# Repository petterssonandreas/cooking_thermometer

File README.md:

# cooking_thermometer

Simple electronics and SW project for creating a digital cooking/meat thermometer.

A probe from an old broken thermometer is used. The probe appears to be an NTC with around 200k resistance at 25C. Tests done at different temps to get a curve for the probe, curve can be found in `adc.c`.

The probe is connected to the HW via a 2.5mm "mono" jack with tip detection.

The processor used is an STM32G0B0KE with 512 kB flash and 144 kB SRAM. It comes in a LQFP32 package.

The product is powered via USB or via a 3.6V Li-ion battery, which is also charged when USB is connected. The battery is recycled from another old product. A small MCP73831 is used for the battery charging.

A small OLED display is used to display temperature and other info.

An active buzzer is used for the alarm functionality.

The system runs on 3.3 V.

# Zephyr installation

### Clone this repo
```
git clone git@github.com:petterssonandreas/cooking_thermometer.git
```

### Create a virtualenv, source it
```
python3 -m venv .venv
source .venv/Scripts/activate
```

### Install west
```
pip3 install west
```

### Init west with local repo, update
```
west init -l cooking_thermometer/
west update
```

### Export CMake
```
west zephyr-export
```

### Install packages
```
west packages pip --install
```

### Install Zephyr SDK
```
west sdk install
```

# Project build and flash
```
west build -p always -b ct_g0b0ke cooking_thermometer/apps/ct/
west flash
```

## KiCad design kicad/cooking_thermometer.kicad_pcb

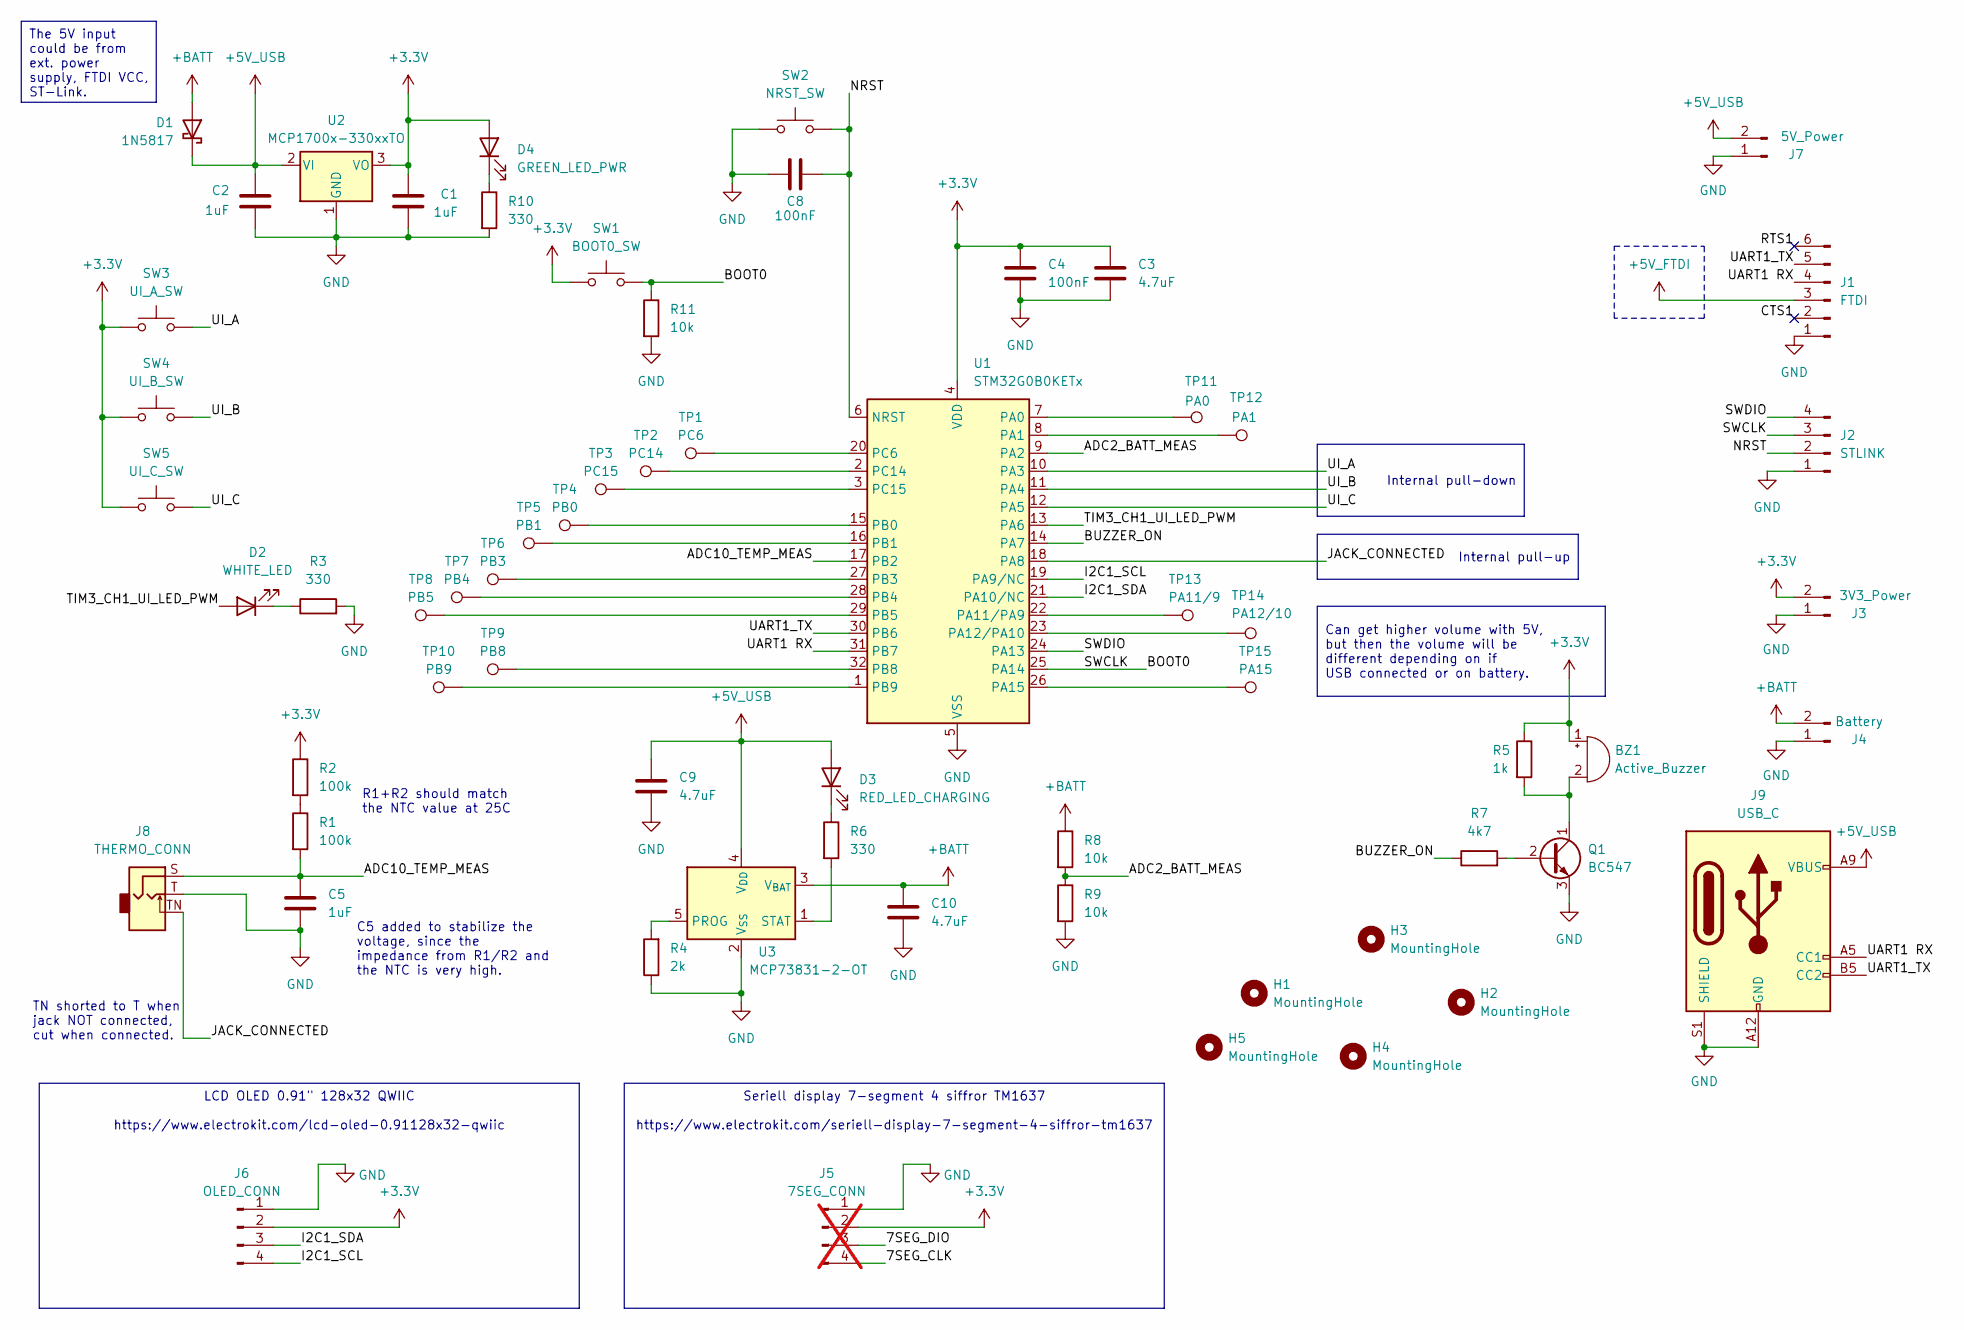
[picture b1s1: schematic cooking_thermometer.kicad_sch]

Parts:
BZ1: Active_Buzzer; Buzzer_12x9.5RM7.6
C1, C2, C5: 1uF; C_1206_3216Metric_Pad1.33x1.80mm_HandSolder
C3, C9, C10: 4.7uF; C_1206_3216Metric_Pad1.33x1.80mm_HandSolder
C4, C8: 100nF; C_1206_3216Metric_Pad1.33x1.80mm_HandSolder
D1: 1N5817; D_DO-41_SOD81_P10.16mm_Horizontal
D2: WHITE_LED; LED_D4.0mm
D3: RED_LED_CHARGING; LED_Rectangular_W5.0mm_H2.0mm
D4: GREEN_LED_PWR; LED_Rectangular_W5.0mm_H2.0mm
H1, H2, H3, H4, H5: MountingHole; MountingHole_3.2mm_M3
J1: FTDI; PinHeader_1x06_P2.54mm_Vertical
J2: STLINK; PinHeader_1x04_P2.54mm_Vertical
J3: 3V3_Power; PinHeader_1x02_P2.54mm_Vertical
J4: Battery; PinHeader_1x02_P2.54mm_Vertical
J5: 7SEG_CONN; PinSocket_1x04_P2.54mm_Vertical; not fitted
J6: OLED_CONN; PinHeader_1x04_P2.54mm_Vertical
J7: 5V_Power; PinHeader_1x02_P2.54mm_Vertical
J8: THERMO_CONN; Jack_Mono_2.5mm_with_Tip-Detect_Electrokit_41010270
J9: USB_C; USB_C_Receptacle_6P_TopMnt_Horizontal_Long_Pads_Electrokit_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
Q1: BC547; TO-92L_Inline_Wide
R1, R2: 100k; R_1206_3216Metric_Pad1.30x1.75mm_HandSolder
R3, R6, R10: 330; R_1206_3216Metric_Pad1.30x1.75mm_HandSolder
R4: 2k; R_1206_3216Metric_Pad1.30x1.75mm_HandSolder
R5: 1k; R_1206_3216Metric_Pad1.30x1.75mm_HandSolder
R7: 4k7; R_1206_3216Metric_Pad1.30x1.75mm_HandSolder
R8, R9, R11: 10k; R_1206_3216Metric_Pad1.30x1.75mm_HandSolder
SW1: BOOT0_SW; SW_PUSH_6mm
SW2: NRST_SW; SW_PUSH_6mm
SW3: UI_A_SW; SW_PUSH_6mm
SW4: UI_B_SW; SW_PUSH_6mm
SW5: UI_C_SW; SW_PUSH_6mm
TP1: PC6; TestPoint_Pad_D2.0mm
TP2: PC14; TestPoint_Pad_D2.0mm
TP3: PC15; TestPoint_Pad_D2.0mm
TP4: PB0; TestPoint_Pad_D2.0mm
TP5: PB1; TestPoint_Pad_D2.0mm
TP6: PB3; TestPoint_Pad_D2.0mm
TP7: PB4; TestPoint_Pad_D2.0mm
TP8: PB5; TestPoint_Pad_D2.0mm
TP9: PB8; TestPoint_Pad_D2.0mm
TP10: PB9; TestPoint_Pad_D2.0mm
TP11: PA0; TestPoint_Pad_D2.0mm
TP12: PA1; TestPoint_Pad_D2.0mm
TP13: PA11/9; TestPoint_Pad_D2.0mm
TP14: PA12/10; TestPoint_Pad_D2.0mm
TP15: PA15; TestPoint_Pad_D2.0mm
U1: STM32G0B0KETx; LQFP-32_7x7mm_P0.8mm_Long_pads
U2: MCP1700x-330xxTO; TO-92_Inline
U3: MCP73831-2-OT; SOT-23-5_HandSoldering

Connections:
+3.3V: BZ1.1 (+), C1.1, C3.1, C4.1, D4.2 (A), J3.2, J5.2, J6.2, R2.1, R5.1, SW1.1, SW3.1, SW4.1, SW5.1, U1.4 (VDD), U2.3 (VO)
+5V_FTDI: J1.3
+5V_USB: C2.1, C9.1, D1.1 (K), D3.2 (A), J7.2, J9.A9 (VBUS), J9.B9 (VBUS), U2.2 (VI), U3.4 (V_{DD})
+BATT: C10.1, D1.2 (A), J4.2, R8.1, U3.3 (V_{BAT})
/ADC2_BATT_MEAS: R8.2, R9.1, U1.9 (PA2)
/ADC10_TEMP_MEAS: C5.1, J8.S, R1.2, U1.17 (PB2)
/BOOT0: J2.3, R11.1, SW1.2, U1.25 (PA14)
/BUZZER_ON: R7.1, U1.14 (PA7)
/CTS1: J1.2
/I2C1_SCL: J6.4, U1.19 (PA9/NC)
/I2C1_SDA: J6.3, U1.21 (PA10/NC)
/JACK_CONNECTED: J8.TN, U1.18 (PA8)
/NRST: C8.2, J2.2, SW2.2, U1.6 (NRST)
/RTS1: J1.6
/SWDIO: J2.4, U1.24 (PA13)
/TIM3_CH1_UI_LED_PWM: D2.2 (A), U1.13 (PA6)
/UART1 RX: J1.4, J9.A5 (CC1), U1.31 (PB7)
/UART1_TX: J1.5, J9.B5 (CC2), U1.30 (PB6)
/UI_A: SW3.2, U1.10 (PA3)
/UI_B: SW4.2, U1.11 (PA4)
/UI_C: SW5.2, U1.12 (PA5)
GND: C1.2, C2.2, C3.2, C4.2, C5.2, C8.1, C9.2, C10.2, J1.1, J2.1, J3.1, J4.1, J5.1, J6.1, J7.1, J8.T, J9.A12 (GND), J9.B12 (GND), J9.S1 (SHIELD), Q1.3 (E), R3.2, R4.1, R9.2, R10.2, R11.2, SW2.1, U1.5 (VSS), U2.1 (GND), U3.2 (V_{SS})
unnamed: BZ1.2 (-), Q1.1 (C), R5.2
unnamed: D2.1 (K), R3.1
unnamed: D3.1 (K), R6.1
unnamed: D4.1 (K), R10.1
unnamed: Q1.2 (B), R7.2
unnamed: R1.1, R2.2
unnamed: TP11.1, U1.7 (PA0)
unnamed: TP12.1, U1.8 (PA1)
unnamed: TP13.1, U1.22 (PA11/PA9)
unnamed: TP14.1, U1.23 (PA12/PA10)
unnamed: TP15.1, U1.26 (PA15)
unnamed: TP4.1, U1.15 (PB0)
unnamed: TP5.1, U1.16 (PB1)
unnamed: TP6.1, U1.27 (PB3)
unnamed: TP7.1, U1.28 (PB4)
unnamed: TP8.1, U1.29 (PB5)
unnamed: TP9.1, U1.32 (PB8)
unnamed: TP10.1, U1.1 (PB9)
unnamed: TP1.1, U1.20 (PC6)
unnamed: TP2.1, U1.2 (PC14)
unnamed: TP3.1, U1.3 (PC15)
unnamed: R4.2, U3.5 (PROG)
unnamed: R6.2, U3.1 (STAT)

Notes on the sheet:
Can get higher volume with 5V, but then the volume will be different depending on if USB connected or on battery.
LCD OLED 0.91" 128x32 QWIIC https://www.electrokit.com/lcd-oled-0.91128x32-qwiic
Internal pull-down
Internal pull-up
The 5V input could be from ext. power supply, FTDI VCC, ST-Link.
Seriell display 7-segment 4 siffror TM1637 https://www.electrokit.com/seriell-display-7-segment-4-siffror-tm1637
TN shorted to T when jack NOT connected, cut when connected.
R1+R2 should match the NTC value at 25C
C5 added to stabilize the voltage, since the impedance from R1/R2 and the NTC is very high.

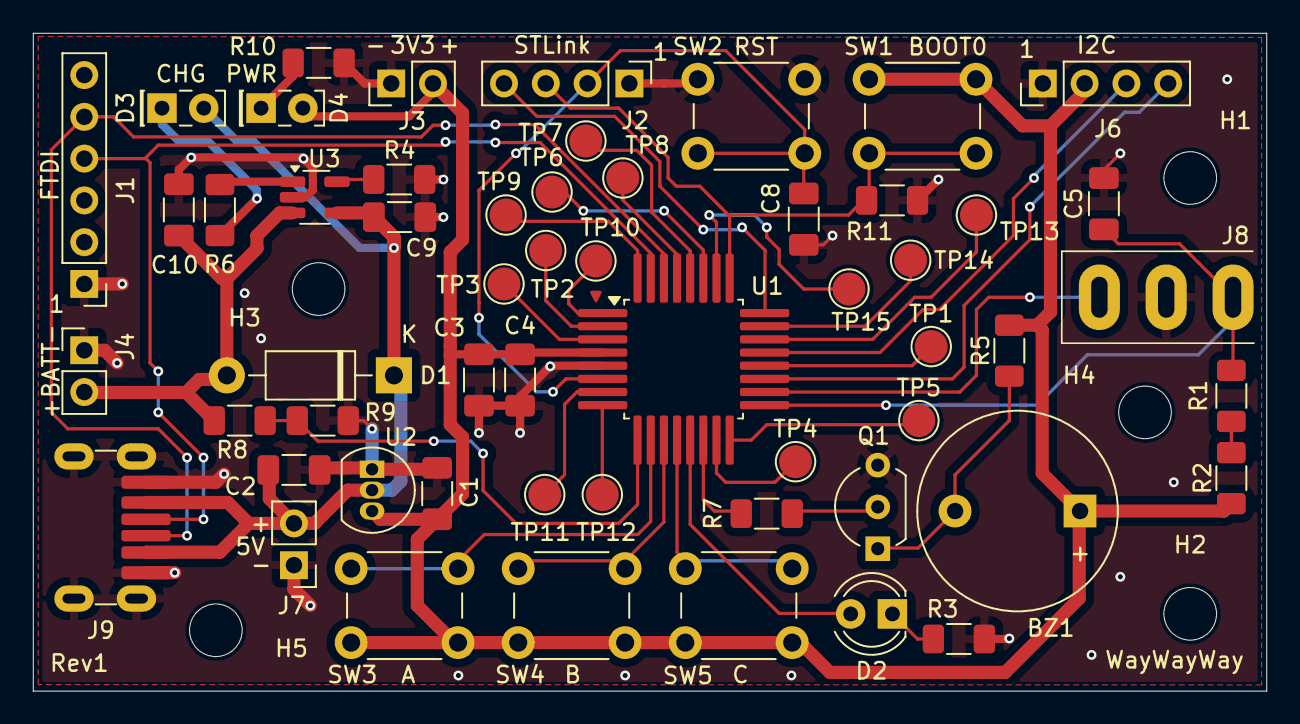
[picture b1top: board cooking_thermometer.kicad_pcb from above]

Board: 2 copper layers, 75.0 x 40.0 mm, 61 parts (0 on the bottom side), 42 nets.

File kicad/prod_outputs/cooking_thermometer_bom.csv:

"Id";"Designator";"Footprint";"Quantity";"Designation";"Supplier and ref";
1;"TP2";"TestPoint_Pad_D2.0mm";1;"PC14";;;
2;"R3,R6,R10";"R_1206_3216Metric_Pad1.30x1.75mm_HandSolder";3;"330";;;
3;"SW4";"SW_PUSH_6mm";1;"UI_B_SW";;;
4;"R8,R9,R1,R2";"R_1206_3216Metric_Pad1.30x1.75mm_HandSolder";4;"100k";;;
5;"SW5";"SW_PUSH_6mm";1;"UI_C_SW";;;
6;"U1";"LQFP-32_7x7mm_P0.8mm_Long_pads";1;"STM32G0B0KETx";;;
7;"C10,C3,C9";"C_1206_3216Metric_Pad1.33x1.80mm_HandSolder";3;"4.7uF";;;
8;"J3";"PinHeader_1x02_P2.54mm_Vertical";1;"3V3_Power";;;
9;"TP8";"TestPoint_Pad_D2.0mm";1;"PB5";;;
10;"R5";"R_1206_3216Metric_Pad1.30x1.75mm_HandSolder";1;"1k";;;
11;"J4";"PinHeader_1x02_P2.54mm_Vertical";1;"Battery";;;
12;"C8,C4";"C_1206_3216Metric_Pad1.33x1.80mm_HandSolder";2;"100nF";;;
13;"TP10";"TestPoint_Pad_D2.0mm";1;"PB9";;;
14;"D1";"D_DO-41_SOD81_P10.16mm_Horizontal";1;"1N5817";;;
15;"D4";"LED_Rectangular_W5.0mm_H2.0mm";1;"GREEN_LED_PWR";;;
16;"J8";"Jack_Mono_2.5mm_with_Tip-Detect_Electrokit_41010270";1;"THERMO_CONN";;;
17;"U3";"SOT-23-5_HandSoldering";1;"MCP73831-2-OT";;;
18;"U2";"TO-92_Inline";1;"MCP1700x-330xxTO";;;
19;"TP13";"TestPoint_Pad_D2.0mm";1;"PA11/9";;;
20;"J9";"USB_C_Receptacle_6P_TopMnt_Horizontal_Long_Pads_Electrokit_41021035";1;"USB_C";;;
21;"TP9";"TestPoint_Pad_D2.0mm";1;"PB8";;;
22;"D3";"LED_Rectangular_W5.0mm_H2.0mm";1;"RED_LED_CHARGING";;;
23;"TP6";"TestPoint_Pad_D2.0mm";1;"PB3";;;
24;"TP5";"TestPoint_Pad_D2.0mm";1;"PB1";;;
25;"J2";"PinHeader_1x04_P2.54mm_Vertical";1;"STLINK";;;
26;"J7";"PinHeader_1x02_P2.54mm_Vertical";1;"5V_Power";;;
27;"R7";"R_1206_3216Metric_Pad1.30x1.75mm_HandSolder";1;"4k7";;;
28;"TP14";"TestPoint_Pad_D2.0mm";1;"PA12/10";;;
29;"R11";"R_1206_3216Metric_Pad1.30x1.75mm_HandSolder";1;"10k";;;
30;"TP1";"TestPoint_Pad_D2.0mm";1;"PC6";;;
31;"BZ1";"Buzzer_12x9.5RM7.6";1;"Passive_Buzzer";;;
32;"C2,C1";"C_1206_3216Metric_Pad1.33x1.80mm_HandSolder";2;"1uF";;;
33;"Q1";"TO-92L_Inline_Wide";1;"BC547";;;
34;"TP4";"TestPoint_Pad_D2.0mm";1;"PB0";;;
35;"TP11";"TestPoint_Pad_D2.0mm";1;"PA0";;;
36;"SW1";"SW_PUSH_6mm";1;"BOOT0_SW";;;
37;"TP12";"TestPoint_Pad_D2.0mm";1;"PA1";;;
38;"TP15";"TestPoint_Pad_D2.0mm";1;"PA15";;;
39;"J1";"PinHeader_1x06_P2.54mm_Vertical";1;"FTDI";;;
40;"J6";"PinHeader_1x04_P2.54mm_Vertical";1;"OLED_CONN";;;
41;"R4";"R_1206_3216Metric_Pad1.30x1.75mm_HandSolder";1;"2k";;;
42;"SW2";"SW_PUSH_6mm";1;"NRST_SW";;;
43;"TP3";"TestPoint_Pad_D2.0mm";1;"PC15";;;
44;"SW3";"SW_PUSH_6mm";1;"UI_A_SW";;;
45;"TP7";"TestPoint_Pad_D2.0mm";1;"PB4";;;
46;"D2";"LED_D4.0mm";1;"WHITE_LED";;;

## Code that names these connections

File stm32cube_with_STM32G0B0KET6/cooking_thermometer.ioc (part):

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Mcu.Name=STM32G0B0KETx
Mcu.Package=LQFP32
Mcu.UserName=STM32G0B0KETx
PA10.Mode=I2C
PA10.Signal=I2C1_SDA
PA13.Mode=Serial_Wire
PA13.Signal=SYS_SWDIO
PA14-BOOT0.Mode=Serial_Wire
PA14-BOOT0.Signal=SYS_SWCLK
PA2.Mode=IN2
PA2.Signal=ADC1_IN2
PA3.GPIOParameters=GPIO_Label
PA3.GPIO_Label=UI_A
PA3.Signal=GPIO_Input
PA4.GPIOParameters=GPIO_Label
PA4.GPIO_Label=UI_B
PA4.Signal=GPIO_Input
PA5.GPIOParameters=GPIO_Label
PA5.GPIO_Label=UI_C
PA5.Signal=GPIO_Input
PA6.GPIOParameters=GPIO_Label
PA6.GPIO_Label=UI_LED
PA6.Signal=GPIO_Output
PA7.Signal=S_TIM3_CH2
PA8.GPIOParameters=GPIO_Label
PA8.GPIO_Label=nJACK_CONN
PA8.Signal=GPIO_Input
PA9.Mode=I2C
PA9.Signal=I2C1_SCL
PB2.Mode=IN10
PB2.Signal=ADC1_IN10
PB6.Mode=Asynchronous
PB6.Signal=USART1_TX
PB7.Mode=Asynchronous
PB7.Signal=USART1_RX
RCC.HSE_VALUE=8000000
RCC.SYSCLKFreq_VALUE=16000000
board=custom

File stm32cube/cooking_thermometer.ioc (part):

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Mcu.Name=STM32F070F6Px
Mcu.Package=TSSOP20
Mcu.UserName=STM32F070F6Px
PA0.GPIOParameters=GPIO_Label
PA0.GPIO_Label=UI_LED
PA0.Signal=GPIO_Output
PA1.GPIOParameters=GPIO_Label
PA1.GPIO_Label=ADC1_BATT_MEAS
PA1.Mode=IN1
PA1.Signal=ADC_IN1
PA10.Mode=Asynchronous
PA10.Signal=USART1_RX
PA13.Mode=Serial_Wire
PA13.Signal=SYS_SWDIO
PA14.Mode=Serial_Wire
PA14.Signal=SYS_SWCLK
PA2.GPIOParameters=GPIO_PuPd,GPIO_Label
PA2.GPIO_Label=UI_B
PA2.GPIO_PuPd=GPIO_PULLDOWN
PA2.Signal=GPIO_Input
PA3.GPIOParameters=GPIO_PuPd,GPIO_Label
PA3.GPIO_Label=UI_A
PA3.GPIO_PuPd=GPIO_PULLDOWN
PA3.Signal=GPIO_Input
PA4.GPIOParameters=GPIO_Label
PA4.GPIO_Label=TIM14_CH1_BUZZER_PWM
PA4.Signal=S_TIM14_CH1
PA5.GPIOParameters=GPIO_PuPd,GPIO_Label
PA5.GPIO_Label=UI_C
PA5.GPIO_PuPd=GPIO_PULLDOWN
PA5.Signal=GPIO_Input
PA7.GPIOParameters=GPIO_PuPd,GPIO_Label
PA7.GPIO_Label=nJACK_CONNECTED
PA7.GPIO_PuPd=GPIO_PULLUP
PA7.Signal=GPIO_Input
PA9.Mode=Asynchronous
PA9.Signal=USART1_TX
PB1.GPIOParameters=GPIO_Label
PB1.GPIO_Label=ADC9_TEMP_MEAS
PB1.Mode=IN9
PB1.Signal=ADC_IN9
PF0-OSC_IN.Mode=I2C
PF0-OSC_IN.Signal=I2C1_SDA
PF1-OSC_OUT.Mode=I2C
PF1-OSC_OUT.Signal=I2C1_SCL
board=custom

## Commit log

2024-08-04 Add STM32Cube file with pinout, no RTOS stuff done yet
2024-08-04 Add Kicad files, ignore caches and such
2024-08-04 Update Readme with basic info
2024-08-04 Add passive buzzer to schematic, layout, stm32cube
2024-08-08 Enable freeRTOS, use cmake
2024-08-08 Generate code from STM32CubeMX
2024-08-08 Add build/ to gitignore
2024-08-08 Ignore build dirs, and add compile_commands.json link
2024-08-09 Rearrange signals to better fit board
2024-08-09 Regenerate with new signals
2024-08-11 Edit schematic for nrf52810
2024-08-11 Change schematic/layout to stm32g0b0ke (LQFP32)
2024-08-22 Change to longer pads and some other adjustments
2024-08-22 Add stm32cubemx file
2024-08-24 Add +- to battery connection
2024-08-24 Remove old stm32cube, create new for stm32g0b0ke
2024-08-24 Change 2.5mm jack, make the board bigger, add mounting holes. Some rewiring.
2024-08-25 Add extra series on pullup NTC. Move stuff around.
2024-08-25 Set min track clearance to 6mils
2024-08-25 Do some testing with buzzer and OLED
2024-08-25 Final silk fixes
2024-08-25 Create all necessary outputs for rev1 production
2024-08-29 Use bare-metal instead of FreeRTOS
2024-10-20 Add west manifest
2024-10-20 Add board with only basic stuff
    Works with basic blinky sample
2024-10-20 Add simple app
2024-12-15 Add install to readme
2024-12-15 Change to deferred logs
2024-12-27 Use pwm led, and add buzzer gpio
2024-12-27 Add clangd to avoid some warnings in vscode
2024-12-27 Add SVD file
2024-12-27 Add .vscode
2024-12-27 Add KiCad lock files to gitignore
2024-12-27 Add display on i2c
2024-12-28 Move display to another file
2024-12-28 Add RTC and time module
2024-12-28 Add ADC
2024-12-29 Get temperature from NTC
2024-12-29 Add jack/probe check, improve display
2024-12-29 Add battery level calc and display
2024-12-29 Add target temperature and ability to set it
2024-12-29 Add target temp alarm func
2024-12-30 Update schematic and board
    Add C5 for temperature input stabilization
    Rename UI led and buzzer to correctly denote PWM usage
2025-01-01 Add battery shell cmd
2025-01-01 Change how the alarm sounds
